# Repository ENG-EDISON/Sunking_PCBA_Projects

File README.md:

# Sunking_PCBA_Projects
This repository contains SUNKING developed PCBAs

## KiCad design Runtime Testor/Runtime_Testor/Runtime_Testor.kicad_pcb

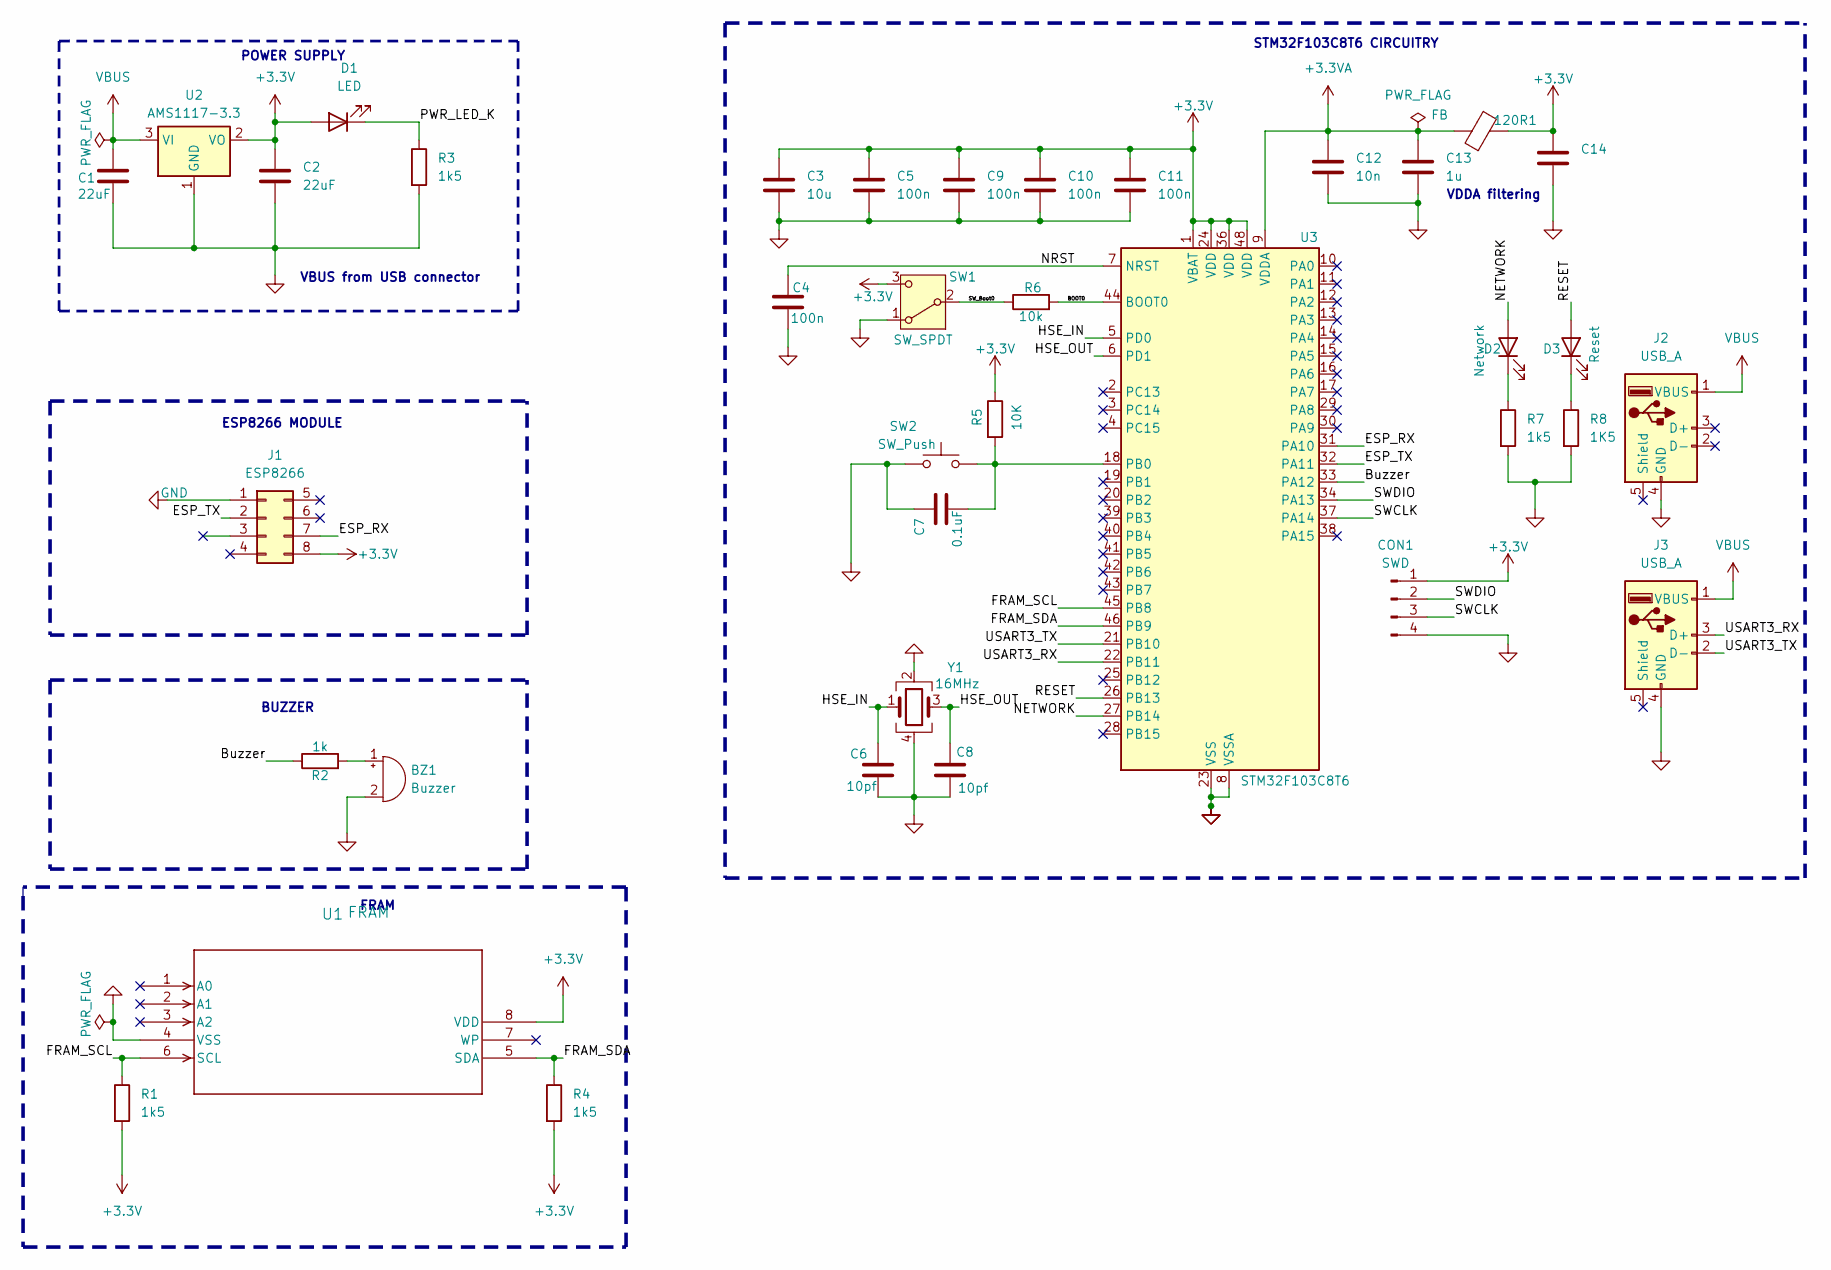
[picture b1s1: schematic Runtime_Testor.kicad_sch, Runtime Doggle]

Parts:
120R1: FB; L_0603_1608Metric
BZ1: Buzzer; MagneticBuzzer_Kingstate_KCG0601
C1, C2: 22uF; C_0805_2012Metric
C3: 10u; C_0603_1608Metric
C4, C5, C9, C10, C11: 100n; C_0402_1005Metric
C6, C8: 10pf; C_0402_1005Metric
C7: 0.1uF; C_0402_1005Metric
C12: 10n; C_0402_1005Metric
C13, C14: 1u; C_0402_1005Metric
CON1: SWD; PinHeader_1x04_P2.54mm_Vertical
D1: LED; LED_0603_1608Metric
D2: Network; LED_0603_1608Metric
D3: Reset; LED_0603_1608Metric
J1: ESP8266; PinSocket_2x04_P2.54mm_Vertical
J2: USB_A; USB_A_CNCTech_1001-011-01101_Horizontal
J3: USB_A; USB_A_Molex_67643_Horizontal
R1, R3, R4, R7: 1k5; R_0402_1005Metric
R2: 1k; R_0402_1005Metric
R5: 10K; R_0402_1005Metric
R6: 10k; R_0402_1005Metric
R8: 1K5; R_0402_1005Metric
SW1: SW_SPDT; SW_Slide_SPDT_Angled_CK_OS102011MA1Q
SW2: SW_Push; SW_Tactile_SPST_Angled_PTS645Vx39-2LFS
U1: FRAM; FPT-8P-M08_FUJ
U2: AMS1117-3.3; SOT-223-3_TabPin2
U3: STM32F103C8T6; LQFP-48_7x7mm_P0.5mm
Y1: 16MHz; Crystal_SMD_0603-4Pin_6.0x3.5mm

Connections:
+3.3V: 120R1.2, C2.1, C3.1, C5.1, C9.1, C10.1, C11.1, C14.1, CON1.1, D1.2 (A), J1.8, R1.2, R4.2, R5.1, SW1.3 (C), U1.8 (VDD), U2.2 (VO), U3.1 (VBAT), U3.24 (VDD), U3.36 (VDD), U3.48 (VDD)
+3.3VA: 120R1.1, C12.1, C13.1, U3.9 (VDDA)
/BOOT0: R6.2, U3.44 (BOOT0)
/Buzzer: R2.1, U3.33 (PA12)
/ESP_RX: J1.7, U3.31 (PA10)
/ESP_TX: J1.2, U3.32 (PA11)
/FRAM_SCL: R1.1, U1.6 (SCL), U3.45 (PB8)
/FRAM_SDA: R4.1, U1.5 (SDA), U3.46 (PB9)
/HSE_IN: C6.1, U3.5 (PD0), Y1.1
/HSE_OUT: C8.1, U3.6 (PD1), Y1.3
/NETWORK: D2.2 (A), U3.27 (PB14)
/NRST: C4.1, U3.7 (NRST)
/PWR_LED_K: D1.1 (K), R3.1
/RESET: D3.2 (A), U3.26 (PB13)
/SWCLK: CON1.3, U3.37 (PA14)
/SWDIO: CON1.2, U3.34 (PA13)
/SW_Boot0: R6.1, SW1.2 (B)
/USART3_RX: J3.3 (D+), U3.22 (PB11)
/USART3_TX: J3.2 (D-), U3.21 (PB10)
GND: BZ1.2 (-), C1.2, C2.2, C3.2, C4.2, C5.2, C6.2, C7.2, C8.2, C9.2, C10.2, C11.2, C12.2, C13.2, C14.2, CON1.4, J1.1, J2.4 (GND), J3.4 (GND), R3.2, R7.2, R8.2, SW1.1 (A), SW2.1, U1.4 (VSS), U2.1 (GND), U3.8 (VSSA), U3.23 (VSS), U3.35 (VSS), U3.47 (VSS), Y1.2, Y1.4
unnamed: BZ1.1 (+), R2.2
unnamed: D2.1 (K), R7.1
unnamed: D3.1 (K), R8.1
unnamed: C7.1, R5.2, SW2.2, U3.18 (PB0)
VBUS: C1.1, J2.1 (VBUS), J3.1 (VBUS), U2.3 (VI)

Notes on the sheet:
STM32F103C8T6 CIRCUITRY
POWER SUPPLY
BUZZER
VDDA filtering
ESP8266 MODULE
FRAM
VBUS from USB connector

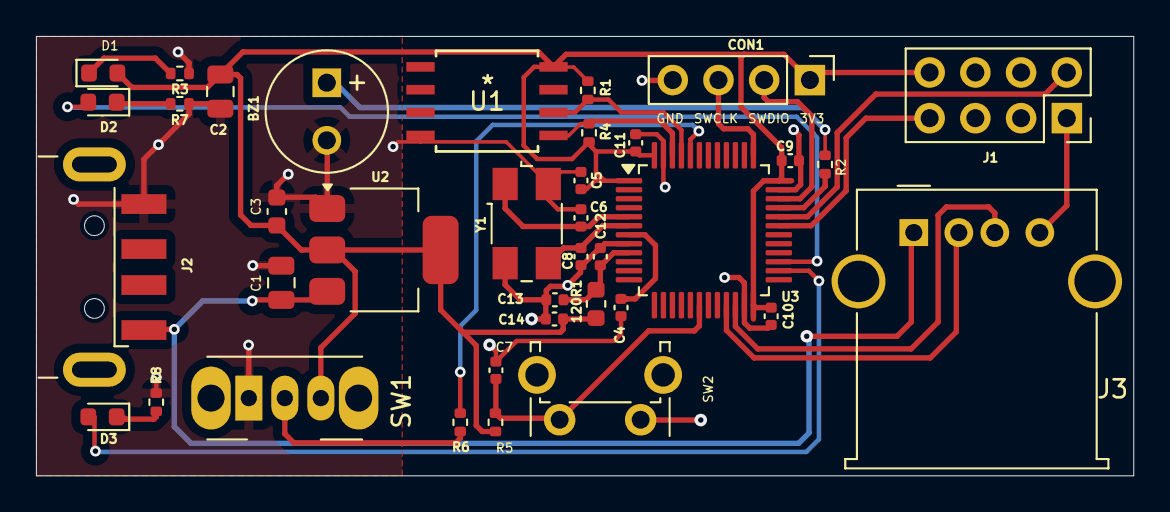
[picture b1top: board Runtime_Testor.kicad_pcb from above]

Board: 2 copper layers, 61.0 x 24.4 mm, 37 parts (0 on the bottom side), 25 nets.

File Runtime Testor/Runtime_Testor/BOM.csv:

Reference,Value,Datasheet,Footprint,Qty,DNP
120R1,FB,~,Inductor_SMD:L_0603_1608Metric,1,
BZ1,Buzzer,~,Buzzer_Beeper:MagneticBuzzer_Kingstate_KCG0601,1,
"C1,C2",22uF,~,Capacitor_SMD:C_0805_2012Metric,2,
C3,10u,~,Capacitor_SMD:C_0603_1608Metric,1,
"C4,C5,C9,C10,C11",100n,~,Capacitor_SMD:C_0402_1005Metric,5,
"C6,C8",10pf,~,Capacitor_SMD:C_0402_1005Metric,2,
C7,0.1uF,~,Capacitor_SMD:C_0402_1005Metric,1,
C12,10n,~,Capacitor_SMD:C_0402_1005Metric,1,
"C13,C14",1u,~,Capacitor_SMD:C_0402_1005Metric,2,
CON1,SWD,~,Connector_PinHeader_2.54mm:PinHeader_1x04_P2.54mm_Vertical,1,
D1,LED,~,LED_SMD:LED_0603_1608Metric,1,
D2,LED,~,LED_SMD:LED_0603_1608Metric,1,
D3,LED,~,LED_SMD:LED_0603_1608Metric,1,
J2,USB_A,~,Connector_USB:USB_A_CNCTech_1001-011-01101_Horizontal,1,
"R1,R3,R4,R7",1k5,~,Resistor_SMD:R_0402_1005Metric,4,
R2,1k,~,Resistor_SMD:R_0402_1005Metric,1,
R5,10K,~,Resistor_SMD:R_0402_1005Metric,1,
R6,10k,~,Resistor_SMD:R_0402_1005Metric,1,
R8,1K5,~,Resistor_SMD:R_0402_1005Metric,1,
SW1,SW_SPDT,~,Button_Switch_THT:SW_Slide_SPDT_Straight_CK_OS102011MS2Q,1,
SW2,SW_Push,~,Button_Switch_THT:SW_Tactile_SPST_Angled_PTS645Vx39-2LFS,1,
U1,FRAM,MB85RC256VPF-G-JNERE2,footprints:FPT-8P-M08_FUJ,1,
U2,AMS1117-3.3,http://www.advanced-monolithic.com/pdf/ds1117.pdf,Package_TO_SOT_SMD:SOT-223-3_TabPin2,1,
USART3,CON,~,Connector_PinHeader_2.54mm:PinHeader_1x04_P2.54mm_Vertical,1,
Y1,16MHz,~,Crystal:Crystal_SMD_0603-4Pin_6.0x3.5mm,1,
ESP8266 Modules,ESP-01S,https://www.alibaba.com/product-detail/ESP01-WIFI-wireless-m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,,,

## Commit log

2025-08-22 tester PCBA
2025-08-22 Added USB Port for UART communication
